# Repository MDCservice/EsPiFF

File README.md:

# EsPiFF
An ESP32 in the Raspberry Pi form factor

## Meet the EsPiFF - The ESP32 in the Raspberry Pi 4 form factor

For applications, where the Raspberry Pi 4 is not robust enough, or take too much power, you can consider the EsPiFF as an option.
The EsPiFF (V2) brings
 - ESP32-WROVER with dual core, 8MB PSRAM, 16 MB Flash
 - Ethernet wired and Wifi (Wifi need an external antenna with an uFL connector)
 - SD-card for data storage
 - up to 3 UARTs
 - an USB-C connector for power supply up to 5V, 3A
 - a Rasperry Pi header with 40 pin, compatible to all Raspberry Pi HATs

The EsPiFF V3 will bring the following 
 - an RP2040 IO-processor additional to the ESP32
 - 2kByte FRAM for high-speed permanent storage
 - RTC Realtime clock
 - USB-A connector for USB-Host

EsPiFF-PLC

## Why an ESP32 in the Raspberry Pi Form Factor?

We decided to build an alternative to the Raspberry Pi for our projects and products. As many others we were using the Raspberry Pi in our products, adding electronic payment to existing vending machines and coffee machines, in RFID solutions to read RFID tags in laundry and other application. 
While it was easy to get a solution up and running in a short time, over time we got a lot of problems resulting from using the Pi.
A key problem of the Pi's design is, to rely on an SD-card. The SD-cards are made for digital cameras, to write on them a few times. A Linux system like the Pi on the other hand, is writing permanent its log files and swap partition or to the SD-card. As a result, after some months the SD-card broke and the application crashed. High-end industrial SD-card lasted longer, but finally still broke. An industrial controller simply can not base on a SD-card.
The PI Operating system is also great for fast bring-up of a solution, but its more and more focused on media streaming then real-time tasks. It gets more and more overloaded with each new version.
So we made the decision, to build a replacement, which is focused on high-reliability, but still enable the use of Raspberry Pi universum of add-ons, like HATs and enclosures. We choose the ESP32 dual core, 2x240MHz WROVER module with 8MB PSRAM and 16MB Flash.  The EsPiFF, the **Es**p32 in Raspberry **Pi** **F**orm **F**actor was born.

## History
### Version 1
The first version of the EsPiFF was born in a time, where all Ethernet Phy chips was unavailable. Our first prototype used a Waveshare LAN8720 module. Chip crysis! Interestingly, even no LAN8720 chips could be bought anywhere, but the modules was still available. Because the Waveshare module did not route the enable signal to the pin header, but left one pin unconnected on the pin header, we had to solder a wire from the oscillator to that unused pin on the header. After these, the board run well, and do so till now. We added 4 high side switches, and digital inputs to operate 4 door locks. These are the 4 white connectors opposite the RJ45 connectors. The Version 1 had the WROOM module of the ESP32.  

Picture: the Version 1 of the EsPiFF

We ported the PostgreSQL client libray, based on [SimplePgPSQL](https://github.com/ethanak/SimplePgSQL) to the EsPiFF, what worked very well, even with the limited RAM and Flash. Not only SELECT, INSERT and UPDATE work, but also the brilliant PostgreSQL feature NOTIFY. As a result, the EsPiFF dont need to poll the PostgreSQL server, but get notified instead. We could define a trigger in PostgreSQL, and notify other EsPiFF board. Thats very cool.

Because of the ongoing chip crysis, we only select parts, what are available. 

### Version 2

After the LAN8720 chips got available again, we decided to make a new board revision. These are the current boards. We used the ESP32-WROVER module, for additional 8MB PSRAM and 16MB Flash. We also added an SD-card. Unfortunately, we used the wrong pinout, make it very difficult to change the SD-card. An other issue was a missing pull-up resistor on the LAN8720. 
We changed the USB connector to a Type-C connector, and configured it so, that 5V and up to 3A can be taken. Thats a big improvement, raising the available power from 0.5W to 15W. We removed the 4 door lock connectors, and put them on a HAT. 
Since version 1 we have a "Chafon-Connector", next to the USB connector. It is to connect the Chafon RFID Rain(UHF) modules. Additional, we replaced the UART pin headers with more robust JST connectors, left and right of the SD-card. 

We could also compile and flash the Apache Nuttx operating system on the new board. A growing number of people are using ESP32-WROVER boards together with Nuttx as OS. This offers an somehow easy path of porting Linux and Raspberry Pi software on ESP32+Nuttx. 

### Version 3
This is the planned final version. Additional to the fix of the 2 known issues, we plan the following:
 - adding a I2C-RTC: a real-time clock will be needed for planned PLC usage.
 - adding a 2kByte FRAM: again for PLC application, a fast and non-volatile memory is needed. It offers near infinity write/read cycles compared to flash.
 - replace the WROVER module with a version with u.FL/IPEX connector. This enables an external antenna, longer range, mounting inside a metal enclosure with the antenna outside the enclosure.
 - adding a RP2040 co-processor. The ESP32 just not have enough pins free, to operate all the pins on the Raspberry Pi 40pin header. The last solution with the I2C port expander is too slow and unflexible. The much more powerfull RP2040 will solve these problem. It also offers an USB host port!
 - add a USB-A connector, to program the RP2040, and to enable to connect USB devices like keyboard, mouse, USB-sticks and so on. 
 - add an HMI connector next to the SDcard socket. This is for our upcomming TFT displays, but can be used for UART based TFTs like the Nextion as well. 

This is the current progress. We managed, to bring all the functionality on the board. We selected a 6 layer PCB, for best signal integrity.

The ESP32 can communicate with the RP2040 via SPI, where the ESP32 is the SPI master. Depend on the requirements, the communication protocol can be implemented application specific, with ether the Espressif IDF or Arduino IDE. Or an existing SPI driver from, for example NuttX, could be used on the ESP side, and the RP2040 emulating for example an SD card or a SPI Flash.

One more option is to run [Firmata](https://github.com/firmata/ConfigurableFirmata) on the RP2040. This is a popular way for Arduino developers, to remote control and Arduino/RP2040 from a host computer, here the ESP32. For now, Firmata only supports UART communication, whats is also possible on the EsPiFF.

Because all pins on both the ESP32 and the RP2040 are used already, there are no decidated interupt pins between ESP32 and RP2040. The software should implement software interupts, when i.e. the receiving buffer reaches a certain level. 

We finally replaced the LAN8720 Ethernet PHY by an IP101, as used in the Espressif Ethernet reference design. The LAN8720 showed stability problems, in combination with the ESP32-WROVER (it is working well with the ESP32-WROOM). Other projects with the ESP32-WROVER - LAN8720 combination (wESP, Olimex) seem to had the same problems, and also switched away from the LAN8720. On this point, a big "Thank you" to Ondrej from Espressif for all of his support in this field. 

We also ordered customized cables, for the DF11 and display connectors, what offer DuPont on the opposite side. With these cables, breadbord or Nextion displays, or other 2.54mm headers can easily connected. 

## Typical applications

This example show, how a Nextion 5 inch TFT, a HF RFID reader from Elatec (TWN4), a Chafon 8 channel RAIN UHF-RFID reader and a 3D printed enclosure can form an electronic identification system. We put the source code and the 3D design files into the example folder. Smaller or bigger Nextion TFTs can be used, when you adapt the 3D design. 

The HMI interact with the user, ask him/her to put the HF-RFID card on the card reader. The TWN4 from Elatec is able to read near any LF or HF card, inclding the LEGIC chips used in many high secure access control applications. The TWN4 is inside the 3D printed enclosure, as well as the Nextion TFT.

With the 8 port RAIN UHF reader/writer from Chafon, we can monitor a whole area with up to 8 antennas. We use it to monitor 4 cabinets, other use cases could be the monitoring a whole room/warehouse, or the entrance of buiildings,etc. Chafon offer 1, 4, 8 and 16 port devices, and they are all compatible with the software. 

In our application, we read/write direct to a PostgreSQL database, connected by wired ethernet, thats why we have ported the LibPQ (the PostgreSQL client library) to the ESP32. The use of other techniques, like MQTT, is also possible. 

Picture: the open 3D printed enclsure, showing the Nextion 5'' TFT, and the TWN4 HF RFID reader

After the EsPiFF is now mature enough, we we are preparing a campaign at Crowd Supply. After the Pre-launch page will be available, we will update the info here. Hope you support us on our Crowd Supply campaign!

Please notice, that the ESP32-module PCB antenna can not be used, an external wifi antenna is required. This is because of space restrictions, the RasPi form factor not allow us to make the board larger, and there is simply no space left for the required keepout area for the PCB antenna. Most people will use a metal enclosure, what renders a PCB antenna useless anyway. We still have to use an ESP32-WROVER module containing a PCB antenna, because only these modules have 16 MB Flash, 8 MB PSRAM, and all the features we build in. Other modules, for example the ESP32-S3, does not have Ethernet MII. 

Apache Nuttx can run on the EsPiFF!
Next the wellknown FreeRTOS, there is an other, not so wellknown operating system supporting ESP32 and friends: Apache Nuttx (https://nuttx.apache.org).
It has a very cool feature: runtime loading of ELF files (for example, from SDcard) into RAM, and then execute it in RAM. Very much like Windows/Linux/MacOS are doing it. Imagine, you can send a SDcard to your customer for software-update. Bye bye over the air(OTA) updates in enviroments, where OTA is not allowed.

ESP32 <> RP2040 interconnection

Latest news:
We just finish the layout of the version 3.2, the version the crowd supply backer will get. Few interesting things:
- We added not only Flash footprints for the ESP32, but also a footprint for an unpopulated SPI RAM for the RP2040. If you need up to 64 MBit SPI RAM for the RP2040, you can just mount an easy to solder SOIC-8 IC on the bottom, and you have 30 times(!) the RAM a normal RP2040 have. 

Because several people mention the integrated PCB antenna, the version 3.2 offer at least a basic use of the PCB antenna. Still, the external PCB antenna is the prefered way to use Wifi with the EsPiFF, now to use the integrated PCB antenna as well. 
Keep in mind, that the ESP32-WROVER-IB module requires a solder jumper modification before the PCB antenna can be used. 

Team MDC

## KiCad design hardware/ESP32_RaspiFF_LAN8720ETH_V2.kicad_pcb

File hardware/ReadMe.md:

Hardware V3.1

This is the final schematic and layout for the Crowd Supply campaign.
The LAN8720 Ethernet PHY got replaced by the IP101, after the LAN8720 in combination with the ESP32-WROVER was not working stable.
Additionally, we added an TFT-Display connector for serial displays/HMIs.

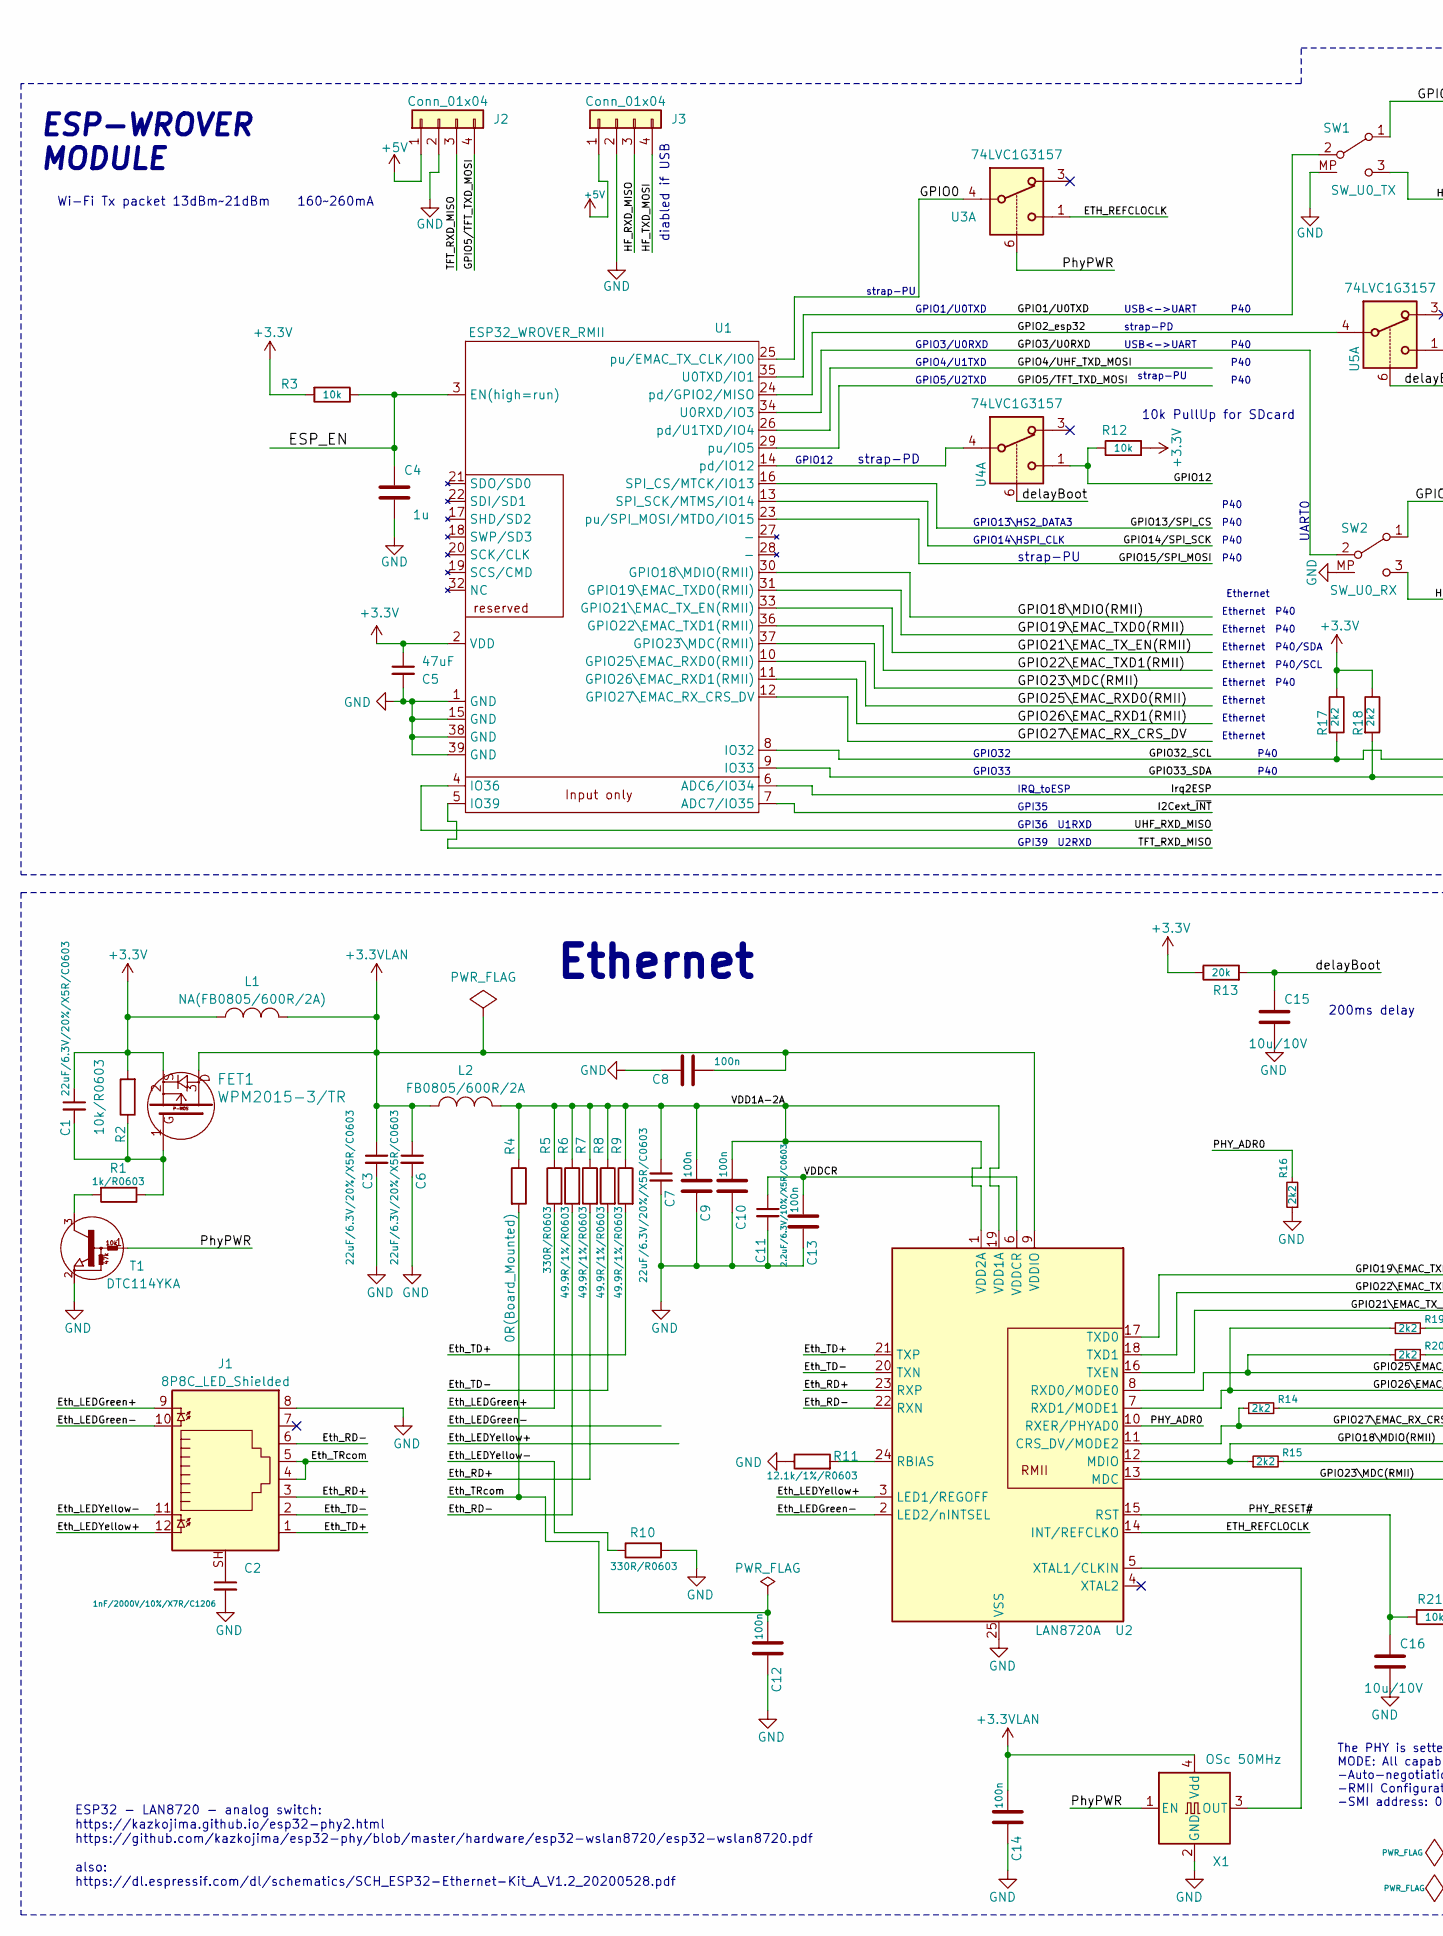
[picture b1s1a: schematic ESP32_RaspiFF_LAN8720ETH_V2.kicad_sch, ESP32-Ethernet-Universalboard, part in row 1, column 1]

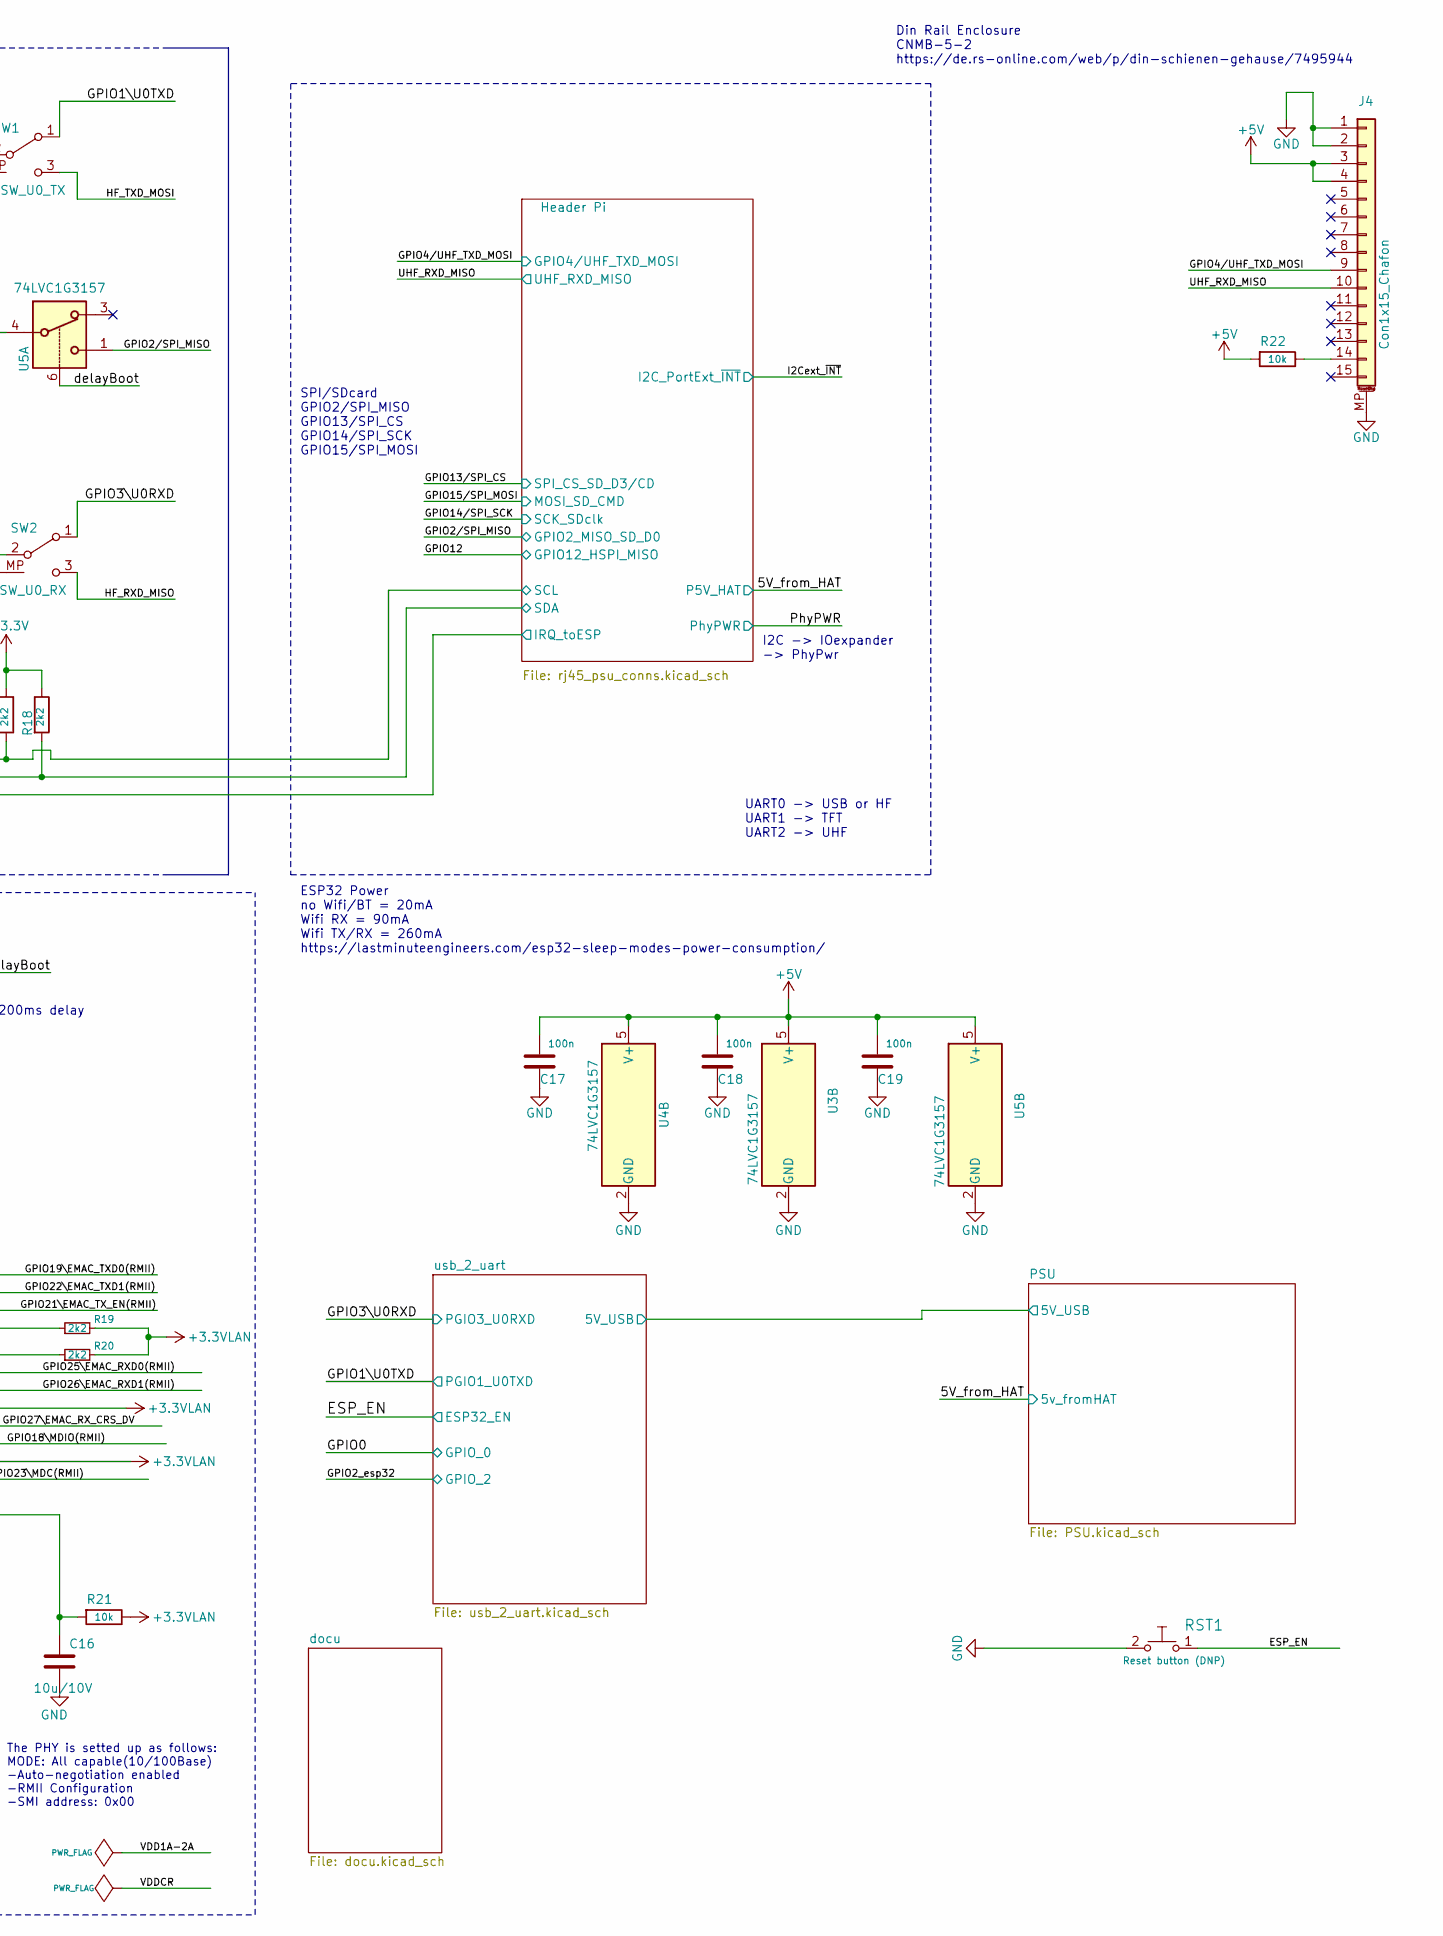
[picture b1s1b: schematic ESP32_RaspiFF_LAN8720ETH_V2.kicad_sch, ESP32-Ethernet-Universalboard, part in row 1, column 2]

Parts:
C1, C3, C6, C7: 22uF/6.3V/20%/X5R/C0603; C_0603_1608Metric
C2: 1nF/2000V/10%/X7R/C1206; C_1206_3216Metric
C4: 1u; C_0603_1608Metric
C5: 47uF; C_0805_5MIL_DWS
C8, C9, C10, C12, C13, C14, C17, C18, C19: 100n; C_0603_1608Metric
C11: 2.2uF/6.3V/10%/X5R/C0603; C_0603_1608Metric
C15, C16: 10u/10V; C_0603_1608Metric
FET1: WPM2015-3/TR; SOT23
J1: 8P8C_LED_Shielded; Hanrun_HR911105A
J2, J3: Conn_01x04; JST_S4B-XH-A1_1x4_P2.5mm
J4: Con1x15_Chafon; mstconn_1.25mm_15pol_ChafonRFID
L1: NA(FB0805/600R/2A); L_0805_5MIL_DWS
L2: FB0805/600R/2A; L_0805_5MIL_DWS
R1: 1k/R0603; R_0603_1608Metric
R2: 10k/R0603; R_0603_1608Metric
R3, R12, R21, R22: 10k; R_0603_1608Metric
R4: 0R(Board_Mounted); R_0603_1608Metric
R5, R10: 330R/R0603; R_0603_1608Metric
R6, R7, R8, R9: 49.9R/1%/R0603; R_0603_1608Metric
R11: 12.1k/1%/R0603; R_0603_1608Metric
R13: 20k; R_0603_1608Metric
R14, R15, R16, R17, R18, R19, R20: 2k2; R_0603_1608Metric
RST1: Reset button (DNP); SW_6.3x3.6
SW1: SW_U0_TX; switch_slide_OnOffOn_MH
SW2: SW_U0_RX; switch_slide_OnOffOn_MH
T1: DTC114YKA; SOT23
U1: ESP32_WROVER_RMII; ESP32-WROVER
U2: LAN8720A; QFN-24-1EP_4x4mm_P0.5mm_EP2.6x2.6mm
U3, U4, U5: 74LVC1G3157; SOT-363_SC-70-6
X1: OSc 50MHz; Oscillator_SMD_Abracon_ASE-4Pin_3.2x2.5mm

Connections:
+3.3VLAN: C3.1, C6.1, C8.2, C14.2, FET1.3, L1.2, L2.1, R14.2, R15.2, R19.2, R20.2, R21.1, U2.9 (VDDIO), X1.4 (Vdd)
+3V3: C1.1, C5.1, FET1.2, L1.1, R2.2, R3.2, R12.2, R13.1, R17.1, R18.1, U1.2 (VDD); also elsewhere on the board
+5V: C17.2, C18.2, C19.2, J2.1, J3.1, J4.3, J4.4, R22.2, U3.5 (V+), U4.5 (V+), U5.5 (V+); also elsewhere on the board
/ESP_EN: C4.1, R3.1, RST1.1, U1.3 (EN(high=run)); also elsewhere on the board
/ETH_REFCLOCLK: U2.14 (INT/REFCLKO), U3.1
/Eth_LEDGreen+: J1.9, R5.2
/Eth_LEDGreen-: J1.10, U2.2 (LED2/nINTSEL)
/Eth_LEDYellow+: J1.12, U2.3 (LED1/REGOFF)
/Eth_LEDYellow-: J1.11, R10.1
/Eth_RD+: J1.3, R7.2, U2.23 (RXP)
/Eth_RD-: J1.6, R6.2, U2.22 (RXN)
/Eth_TD+: J1.1, R9.2, U2.21 (TXP)
/Eth_TD-: J1.2, R8.2, U2.20 (TXN)
/Eth_TRcom: C12.2, J1.4, J1.5, R4.2
/GPIO0: U1.25 (pu/EMAC_TX_CLK/IO0), U3.4; also elsewhere on the board
/GPIO1\U0TXD: SW1.1 (A); also elsewhere on the board
/GPIO1/U0TXD: SW1.2 (B), U1.35 (U0TXD/IO1)
/GPIO2_esp32: U1.24 (pd/GPIO2/MISO), U5.4; also elsewhere on the board
/GPIO2/SPI_MISO: U5.1; also elsewhere on the board
/GPIO3\U0RXD: SW2.1 (A); also elsewhere on the board
/GPIO3/U0RXD: SW2.2 (B), U1.34 (U0RXD/IO3)
/GPIO4/UHF_TXD_MOSI: J4.9, U1.26 (pd/U1TXD/IO4); also elsewhere on the board
/GPIO5/TFT_TXD_MOSI: J2.4, U1.29 (pu/IO5)
/GPIO12: R12.1, U4.1; also elsewhere on the board
/GPIO13/SPI_CS: U1.16 (SPI_CS/MTCK/IO13); also elsewhere on the board
/GPIO14/SPI_SCK: U1.13 (SPI_SCK/MTMS/IO14); also elsewhere on the board
/GPIO15/SPI_MOSI: U1.23 (pu/SPI_MOSI/MTDO/IO15); also elsewhere on the board
/GPIO18\MDIO(RMII): R15.1, U1.30 (GPIO18\MDIO(RMII)), U2.12 (MDIO)
/GPIO19\EMAC_TXD0(RMII): U1.31 (GPIO19\EMAC_TXD0(RMII)), U2.17 (TXD0)
/GPIO21\EMAC_TX_EN(RMII): U1.33 (GPIO21\EMAC_TX_EN(RMII)), U2.16 (TXEN)
/GPIO22\EMAC_TXD1(RMII): U1.36 (GPIO22\EMAC_TXD1(RMII)), U2.18 (TXD1)
/GPIO23\MDC(RMII): U1.37 (GPIO23\MDC(RMII)), U2.13 (MDC)
/GPIO25\EMAC_RXD0(RMII): R20.1, U1.10 (GPIO25\EMAC_RXD0(RMII)), U2.8 (RXD0/MODE0)
/GPIO26\EMAC_RXD1(RMII): R19.1, U1.11 (GPIO26\EMAC_RXD1(RMII)), U2.7 (RXD1/MODE1)
/GPIO27\EMAC_RX_CRS_DV: R14.1, U1.12 (GPIO27\EMAC_RX_CRS_DV), U2.11 (CRS_DV/MODE2)
/GPIO32_SCL: R17.2, U1.8 (IO32); also elsewhere on the board
/GPIO33_SDA: R18.2, U1.9 (IO33); also elsewhere on the board
/HF_RXD_MISO: J3.3, SW2.3 (C)
/HF_TXD_MOSI: J3.4, SW1.3 (C)
/I2Cext_~INT: U1.7 (ADC7/IO35); also elsewhere on the board
/Irq2ESP: U1.6 (ADC6/IO34); also elsewhere on the board
/PHY_ADR0: R16.2, U2.10 (RXER/PHYAD0)
/PHY_RESET#: C16.1, R21.2, U2.15 (RST)
/PhyPWR: T1.1 (B), U3.6, X1.1 (EN); also elsewhere on the board
/TFT_RXD_MISO: J2.3, U1.5 (IO39)
/UHF_RXD_MISO: J4.10, U1.4 (IO36); also elsewhere on the board
/VDD1A-2A: C7.1, C9.2, C10.2, L2.2, R4.1, R5.1, R6.1, R7.1, R8.1, R9.1, U2.1 (VDD2A), U2.19 (VDD1A)
/VDDCR: C11.1, C13.2, U2.6 (VDDCR)
/delayBoot: C15.1, R13.2, U4.6, U5.6
GND: C2.2, C3.2, C4.2, C5.2, C6.2, C7.2, C8.1, C9.1, C10.1, C11.2, C12.1, C13.1, C14.1, C15.2, C16.2, C17.1, C18.1, C19.1, J1.8, J2.2, J3.2, J4.1, J4.2, J4.MP (MountPin), R10.2, R11.1, R16.1, RST1.2, SW1.MP, SW2.MP, T1.2 (E), U1.1 (GND), U1.15 (GND), U1.38 (GND), U1.39 (GND), U2.25 (VSS), U3.2 (GND), U4.2 (GND), U5.2 (GND), X1.2 (GND); also elsewhere on the board
unnamed: C1.2, FET1.1, R1.1, R2.1
unnamed: C2.1, J1.SH
unnamed: J4.14, R22.1
unnamed: R1.2, T1.3 (C)
unnamed: U1.14 (pd/IO12), U4.4
unnamed: R11.2, U2.24 (RBIAS)
unnamed: U2.5 (XTAL1/CLKIN), X1.3 (OUT)

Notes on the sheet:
GPIO13\HS2_DATA3
P40
USB<->UART
diabled if USB
GPIO12
200ms delay
U1RXD
Ethernet
ESP32 Power no Wifi/BT = 20mA Wifi RX = 90mA Wifi TX/RX = 260mA https://lastminuteengineers.com/esp32-sleep-modes-power-consumption/
I2C -> IOexpander -> PhyPwr
SPI/SDcard GPIO2/SPI_MISO GPIO13/SPI_CS GPIO14/SPI_SCK GPIO15/SPI_MOSI
Din Rail Enclosure CNMB-5-2 https://de.rs-online.com/web/p/din-schienen-gehause/7495944
UART0 -> USB or HF UART1 -> TFT UART2 -> UHF
GPI35
The PHY is setted up as follows: MODE: All capable(10/100Base) -Auto-negotiation enabled -RMII Configuration -SMI address: 0x00
ESP32 - LAN8720 - analog switch: https://kazkojima.github.io/esp32-phy2.html https://github.com/kazkojima/esp32-phy/blob/master/hardware/esp32-wslan8720/esp32-wslan8720.pdf also: https://dl.espressif.com/dl/schematics/SCH_ESP32-Ethernet-Kit_A_V1.2_20200528.pdf
strap-PD
IRQ_toESP
GPIO33
GPIO4/U1TXD
Wi-Fi Tx packet 13dBm~21dBm 160~260mA
strap-PU
GPI39
10k PullUp for SDcard
UART0
ESP-WROVER MODULE
GPIO1/U0TXD
GPIO32
U2RXD
GPIO5/U2TXD
GPI36
GPIO3/U0RXD
P40/SDA
P40/SCL
GPIO14\HSPI_CLK

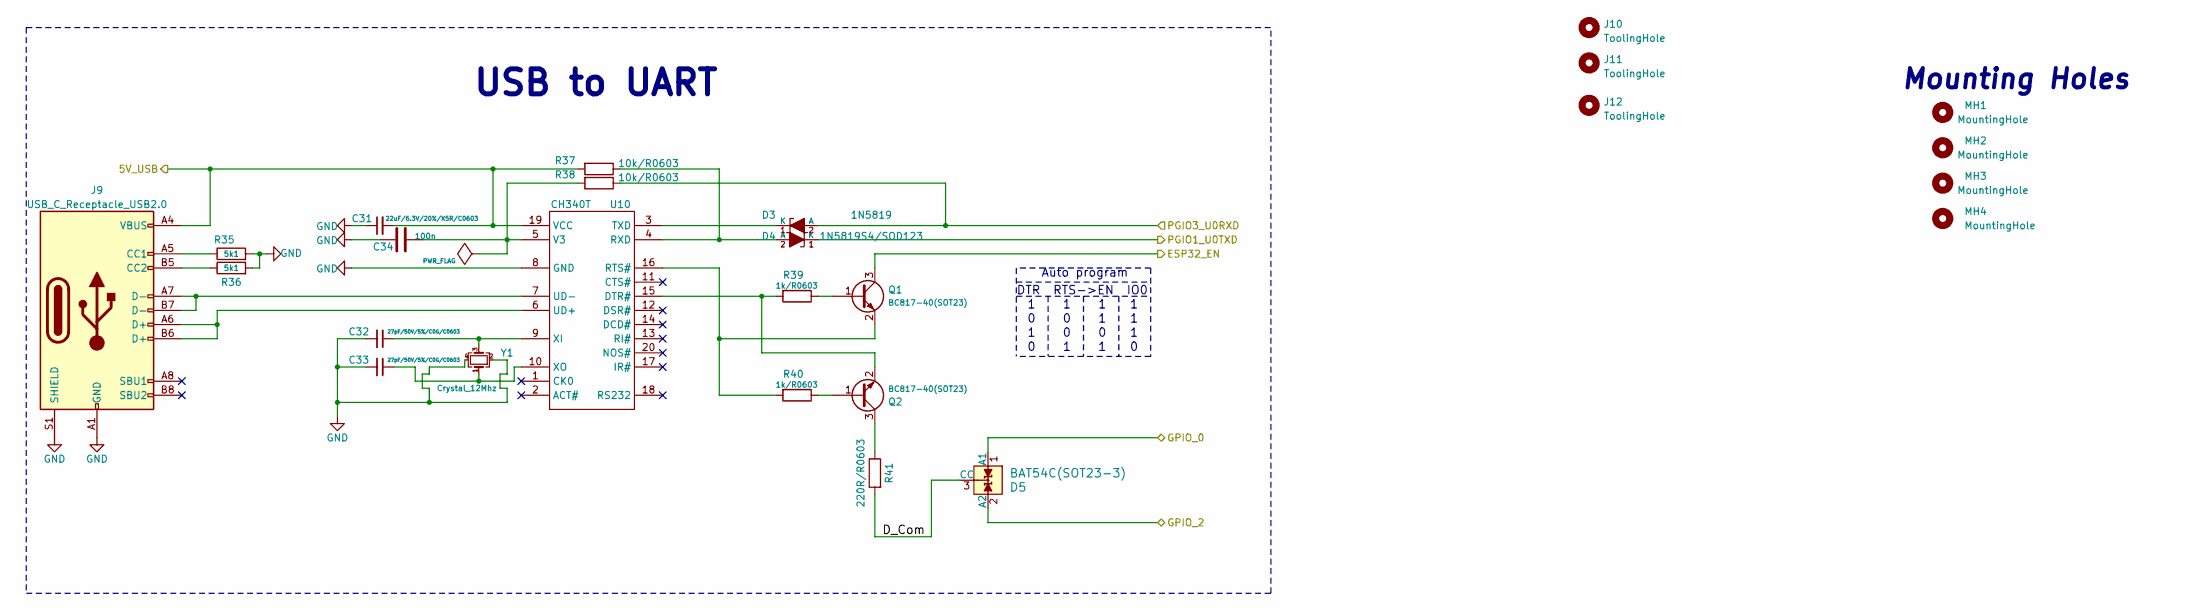
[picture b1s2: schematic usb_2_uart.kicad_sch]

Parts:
C31: 22uF/6.3V/20%/X5R/C0603; C_0603_1608Metric
C32, C33: 27pF/50V/5%/C0G/C0603; C_0603_1608Metric
C34: 100n; C_0603_1608Metric
D3: 1N5819; D_SOD-323
D4: 1N5819S4/SOD123; D_SOD-323
D5: BAT54C(SOT23-3); SOT23-3
J9: USB_C_Receptacle_USB2.0; USB_C_Receptacle_XKB_U262-16XN-4BVC11
J10, J11, J12: ToolingHole; JLCPCB_toolingHole_1.152mm
MH1, MH2, MH3, MH4: MountingHole; MountingHole_3.2mmNPTH
Q1, Q2: BC817-40(SOT23); SOT23
R35, R36: 5k1; R_0603_1608Metric
R37, R38: 10k/R0603; R_0603_1608Metric
R39, R40: 1k/R0603; R_0603_1608Metric
R41: 220R/R0603; R_0603_1608Metric
U10: CH340T; SSOP-20W
Y1: Crystal_12Mhz; Crystal_SMD_3225-4Pin_3.2x2.5mm

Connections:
/ESP_EN: Q1.3 (C); also elsewhere on the board
/GPIO0: D5.1 (A1); also elsewhere on the board
/GPIO1\U0TXD: D4.1 (K); also elsewhere on the board
/GPIO2_esp32: D5.2 (A2); also elsewhere on the board
/GPIO3\U0RXD: D3.2 (A), R38.1; also elsewhere on the board
/PSU/5V_USB: C31.2, J9.A4 (VBUS), J9.A9 (VBUS), J9.B4 (VBUS), J9.B9 (VBUS), R37.2, U10.19 (VCC); also elsewhere on the board
/usb_2_uart/D_Com: D5.3 (CC), R41.2
GND: C31.1, C32.2, C33.2, C34.1, J9.A1 (GND), J9.A12 (GND), J9.B1 (GND), J9.B12 (GND), J9.S1 (SHIELD), R35.2, R36.2, U10.8 (GND), Y1.2, Y1.4; also elsewhere on the board
unnamed: D3.1 (K), U10.3 (TXD)
unnamed: D4.2 (A), R37.1, U10.4 (RXD)
unnamed: J9.A5 (CC1), R35.1
unnamed: J9.B5 (CC2), R36.1
unnamed: J9.A6 (D+), J9.B6 (D+), U10.6 (UD+)
unnamed: J9.A7 (D-), J9.B7 (D-), U10.7 (UD-)
unnamed: Q1.1 (B), R39.1
unnamed: Q1.2 (E), R40.2, U10.16 (RTS#)
unnamed: Q2.1 (B), R40.1
unnamed: Q2.3 (C), R41.1
unnamed: Q2.2 (E), R39.2, U10.15 (DTR#)
unnamed: C34.2, R38.2, U10.5 (V3)
unnamed: C32.1, U10.9 (XI), Y1.3
unnamed: C33.1, U10.10 (XO), Y1.1

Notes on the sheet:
Mounting Holes
USB to UART
Auto program
DTR RTS->EN IO0

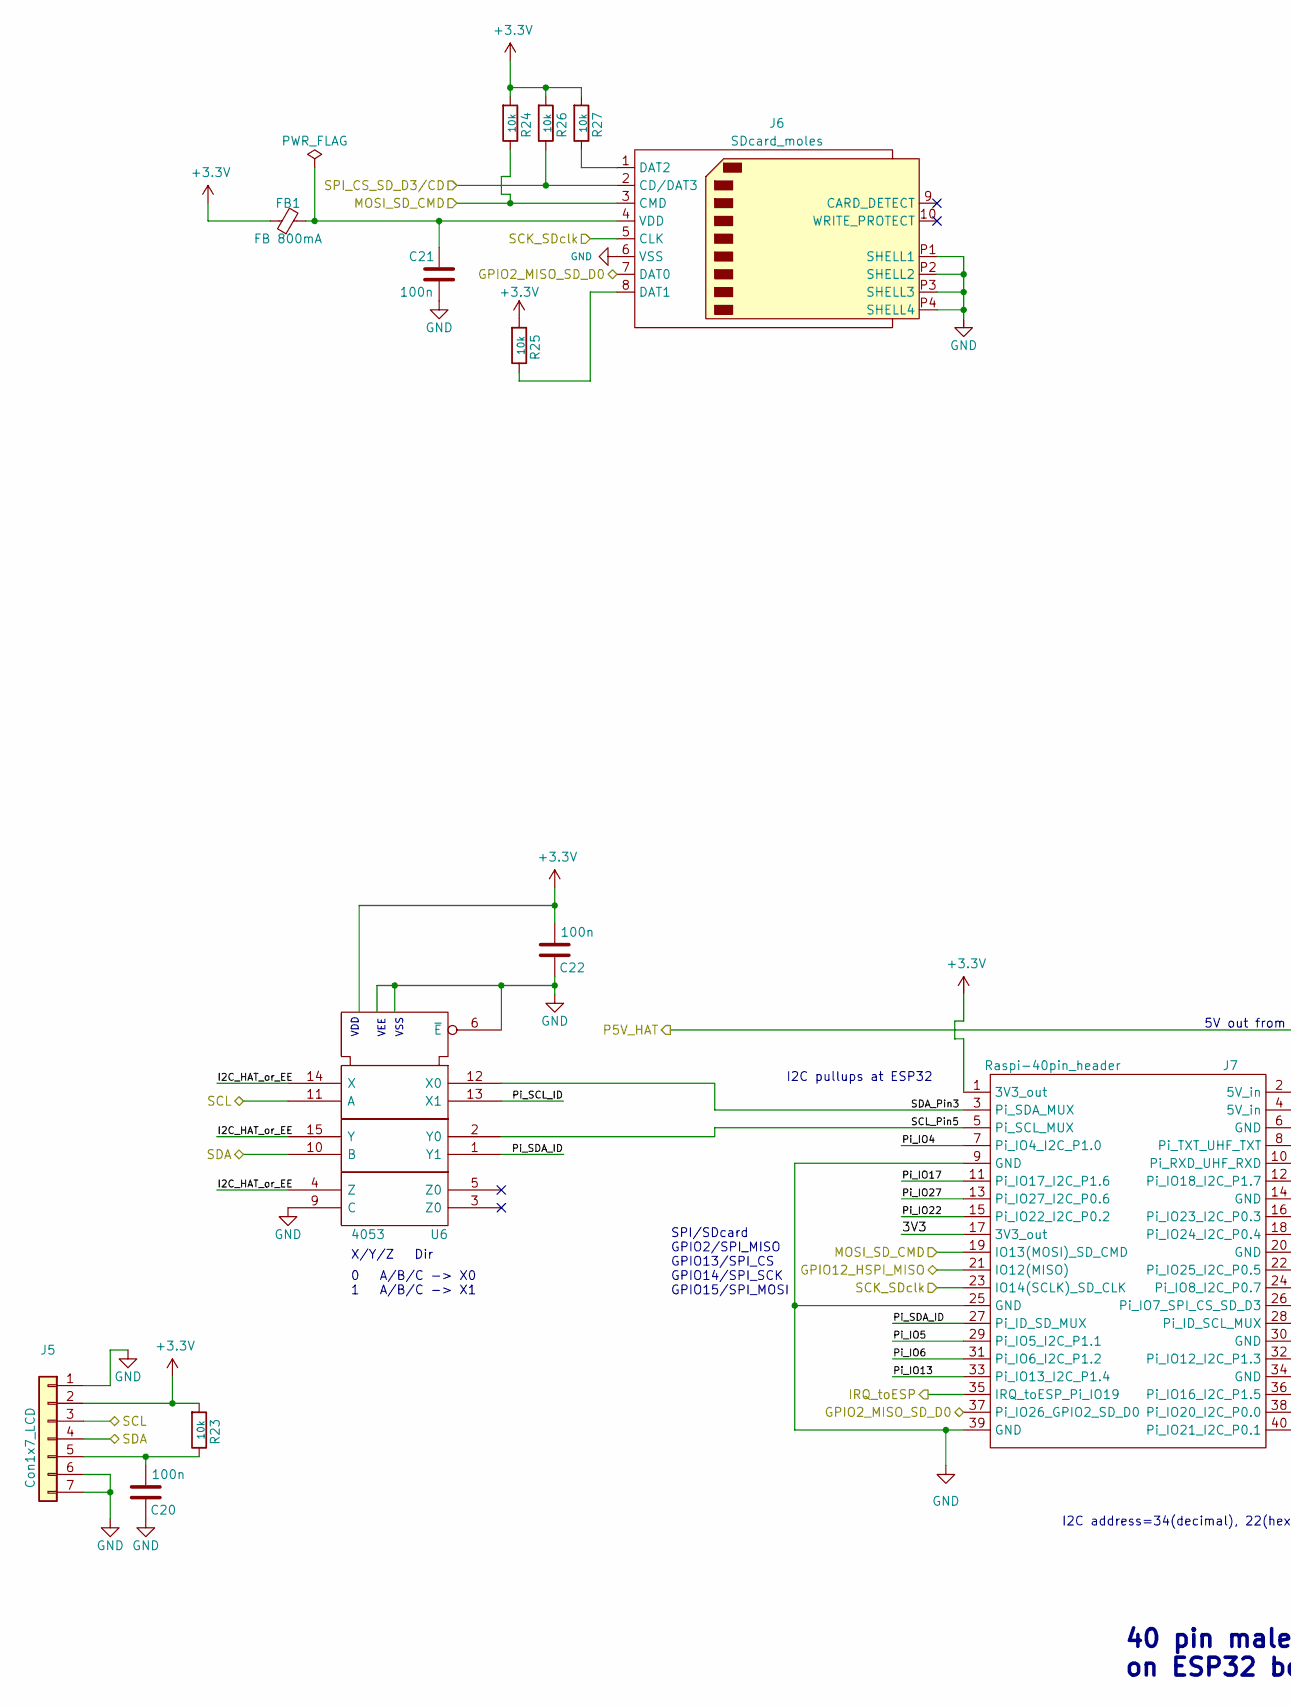
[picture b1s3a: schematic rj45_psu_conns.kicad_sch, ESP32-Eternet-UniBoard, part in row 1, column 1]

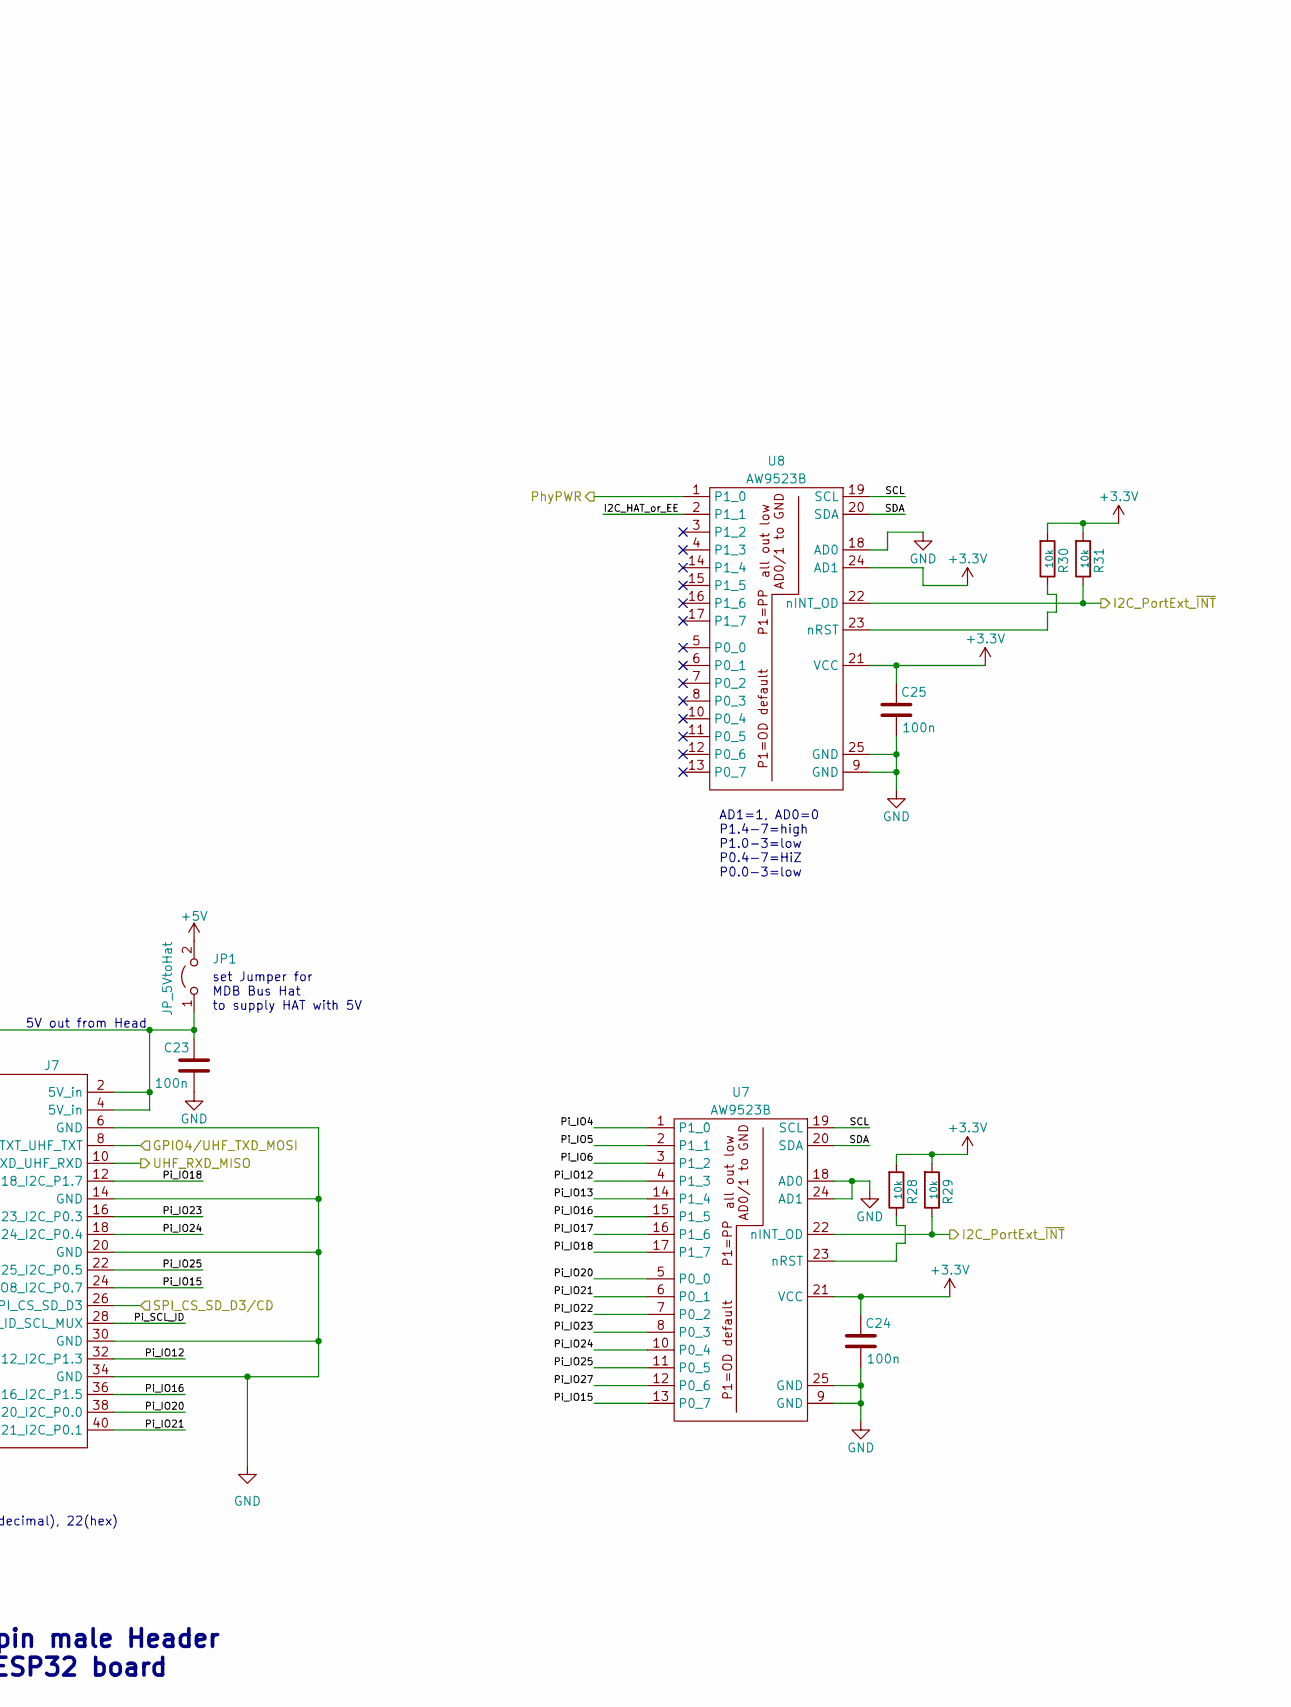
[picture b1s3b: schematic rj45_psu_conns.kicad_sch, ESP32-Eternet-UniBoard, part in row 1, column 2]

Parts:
C20, C21, C22, C23, C24, C25: 100n; C_0603_1608Metric
FB1: FB 800mA; R_0805_2012Metric
J5: Con1x7_LCD; PinHeader_1x07_P2.54mm_Vertical
J6: SDcard_moles; MOLEX_503398-1892
J7: Raspi-40pin_header; PinHeader_2x20_P2.54mm_Vertical
JP1: JP_5VtoHat; PinHeader_1x02_P2.54mm_Vertical
R23, R24, R25, R26, R27, R28, R29, R30, R31: 10k; R_0603_1608Metric
U6: 4053; SOIC-16_3.9x9.9mm_P1.27mm
U7, U8: AW9523B; WQFN-24-1EP_4x4mm_P0.5mm_EP2.6x2.6mm

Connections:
+3V3: C22.2, C24.1, C25.1, FB1.1, J5.2, J7.1 (3V3_out), R23.2, R24.2, R25.2, R26.2, R27.2, R28.2, R29.2, R30.2, R31.2, U6.16 (VDD), U7.21 (VCC), U8.21 (VCC), U8.24 (AD1); also elsewhere on the board
+5V: JP1.2 (B); also elsewhere on the board
/5V_from_HAT: C23.1, J7.2 (5V_in), J7.4 (5V_in), JP1.1 (A); also elsewhere on the board
/GPIO2/SPI_MISO: J6.7 (DAT0), J7.37 (Pi_IO26_GPIO2_SD_D0); also elsewhere on the board
/GPIO4/UHF_TXD_MOSI: J7.8 (Pi_TXT_UHF_TXT); also elsewhere on the board
/GPIO12: J7.21 (IO12(MISO)); also elsewhere on the board
/GPIO13/SPI_CS: J6.2 (CD/DAT3), J7.26 (Pi_IO7_SPI_CS_SD_D3), R26.1; also elsewhere on the board
/GPIO14/SPI_SCK: J6.5 (CLK), J7.23 (IO14(SCLK)_SD_CLK); also elsewhere on the board
/GPIO15/SPI_MOSI: J6.3 (CMD), J7.19 (IO13(MOSI)_SD_CMD), R24.1; also elsewhere on the board
/GPIO32_SCL: J5.3, U6.11 (A), U7.19 (SCL), U8.19 (SCL); also elsewhere on the board
/GPIO33_SDA: J5.4, U6.10 (B), U7.20 (SDA), U8.20 (SDA); also elsewhere on the board
/Header Pi/3V3: J7.17 (3V3_out)
/Header Pi/I2C_HAT_or_EE: U6.4 (Z), U6.14 (X), U6.15 (Y), U8.2 (P1_1)
/Header Pi/Pi_IO4: J7.7 (Pi_IO4_I2C_P1.0), U7.1 (P1_0)
/Header Pi/Pi_IO5: J7.29 (Pi_IO5_I2C_P1.1), U7.2 (P1_1)
/Header Pi/Pi_IO6: J7.31 (Pi_IO6_I2C_P1.2), U7.3 (P1_2)
/Header Pi/Pi_IO12: J7.32 (Pi_IO12_I2C_P1.3), U7.4 (P1_3)
/Header Pi/Pi_IO13: J7.33 (Pi_IO13_I2C_P1.4), U7.14 (P1_4)
/Header Pi/Pi_IO15: J7.24 (Pi_IO8_I2C_P0.7), U7.13 (P0_7)
/Header Pi/Pi_IO16: J7.36 (Pi_IO16_I2C_P1.5), U7.15 (P1_5)
/Header Pi/Pi_IO17: J7.11 (Pi_IO17_I2C_P1.6), U7.16 (P1_6)
/Header Pi/Pi_IO18: J7.12 (Pi_IO18_I2C_P1.7), U7.17 (P1_7)
/Header Pi/Pi_IO20: J7.38 (Pi_IO20_I2C_P0.0), U7.5 (P0_0)
/Header Pi/Pi_IO21: J7.40 (Pi_IO21_I2C_P0.1), U7.6 (P0_1)
/Header Pi/Pi_IO22: J7.15 (Pi_IO22_I2C_P0.2), U7.7 (P0_2)
/Header Pi/Pi_IO23: J7.16 (Pi_IO23_I2C_P0.3), U7.8 (P0_3)
/Header Pi/Pi_IO24: J7.18 (Pi_IO24_I2C_P0.4), U7.10 (P0_4)
/Header Pi/Pi_IO25: J7.22 (Pi_IO25_I2C_P0.5), U7.11 (P0_5)
/Header Pi/Pi_IO27: J7.13 (Pi_IO27_I2C_P0.6), U7.12 (P0_6)
/Header Pi/Pi_SCL_ID: J7.28 (Pi_ID_SCL_MUX), U6.13 (X1)
/Header Pi/Pi_SDA_ID: J7.27 (Pi_ID_SD_MUX), U6.1 (Y1)
/Header Pi/SCL_Pin5: J7.5 (Pi_SCL_MUX), U6.2 (Y0)
/Header Pi/SDA_Pin3: J7.3 (Pi_SDA_MUX), U6.12 (X0)
/I2Cext_~INT: R29.1, R31.1, U7.22 (nINT_OD), U8.22 (nINT_OD); also elsewhere on the board
/Irq2ESP: J7.35 (IRQ_toESP_Pi_IO19); also elsewhere on the board
/PhyPWR: U8.1 (P1_0); also elsewhere on the board
/UHF_RXD_MISO: J7.10 (Pi_RXD_UHF_RXD); also elsewhere on the board
GND: C20.1, C21.2, C22.1, C23.2, C24.2, C25.2, J5.1, J5.6, J5.7, J6.6 (VSS), J6.P1 (SHELL1), J6.P2 (SHELL2), J6.P3 (SHELL3), J6.P4 (SHELL4), J7.6 (GND), J7.9 (GND), J7.14 (GND), J7.20 (GND), J7.25 (GND), J7.30 (GND), J7.34 (GND), J7.39 (GND), U6.6 (~E), U6.7 (VEE), U6.8 (VSS), U6.9 (C), U7.9 (GND), U7.18 (AD0), U7.24 (AD1), U7.25 (GND), U8.9 (GND), U8.18 (AD0), U8.25 (GND); also elsewhere on the board
unnamed: C20.2, J5.5, R23.1
unnamed: J6.8 (DAT1), R25.1
unnamed: J6.1 (DAT2), R27.1
unnamed: C21.1, FB1.2, J6.4 (VDD)
unnamed: R28.1, U7.23 (nRST)
unnamed: R30.1, U8.23 (nRST)

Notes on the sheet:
40 pin male Header on ESP32 board
set Jumper for MDB Bus Hat to supply HAT with 5V
I2C address=34(decimal), 22(hex)
VSS
X/Y/Z Dir
AD1=1, AD0=0 P1.4-7=high P1.0-3=low P0.4-7=HiZ P0.0-3=low
0 A/B/C -> X0 1 A/B/C -> X1
5V out from Head
VDD
VEE
I2C pullups at ESP32
SPI/SDcard GPIO2/SPI_MISO GPIO13/SPI_CS GPIO14/SPI_SCK GPIO15/SPI_MOSI
